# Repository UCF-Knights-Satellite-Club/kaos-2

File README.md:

# kaos-2

KAOS-2 HAB technology demonstration: a high-altitude balloon payload built around a Raspberry Pi Pico flight computer, two Raspberry Pi Zero 2 W camera recorders, and a LightAPRS tracker.

Plan and design notes: [`KAOS_PLAN.md`](KAOS_PLAN.md) and [`KAOS-2_Documentation.md`](KAOS-2_Documentation.md).

## Layout

| Folder | Contents |
|---|---|
| [`Software/`](Software/) | Flight computer code (Pico, Arduino core) |
| [`Electrical/KAOS-2_MainPCB/`](Electrical/KAOS-2_MainPCB/) | Main PCB KiCad project (`KAOS-2_Main.kicad_pro`), with its symbol and footprint library |
| [`Electrical/Symbols/`](Electrical/Symbols/), [`Electrical/Footprints/`](Electrical/Footprints/) | Shared KiCad symbol library and extra footprints (SCD30) |
| [`Test_Modules/`](Test_Modules/) | Bench tests for each module: LightAPRS 2.0 / HAB firmware, BMP388 (C SDK and Arduino), SCD30 (incl. calibration utility), SD card, clock, buzzer, MOSFET, Pico 2 W, and the Pi Zero camera recorder (`Camera/Video_Recorder/`) |
| Root images | Pinouts for the Pico, Pi Zero 2 W and LightAPRS |

## Open items

- **Two flight software versions.** [`Software/KAOS-2.ino`](Software/KAOS-2.ino) (559 lines, last changed 2026-09-21) and [`Software/KAOS-2/KAOS-2.ino`](Software/KAOS-2/KAOS-2.ino) (809 lines, last changed 2026-07-17) differ. Pick the flight version and delete or archive the other.
- **Not yet on GitHub:** the APRS PCB layout and the radio filter test board.
- The main PCB's symbol library (`Electrical/KAOS-2_MainPCB/KAOS-2.kicad_sym`) and the shared one (`Electrical/Symbols/KAOS-2.kicad_sym`) have drifted apart; merge them into one.

## History

Imported from [ColdBloodV/KSC](https://github.com/ColdBloodV/KSC) (`KAOS-2/`) with its commit history. Content from unmerged branches there was added too: the SCD30 calibration utility (`Star-Eater-patch-4`), the BMP_C README (`Star-Eater-patch-2`) and a `2Wscript.py` comment fix (`ColdBloodV-patch-1`).

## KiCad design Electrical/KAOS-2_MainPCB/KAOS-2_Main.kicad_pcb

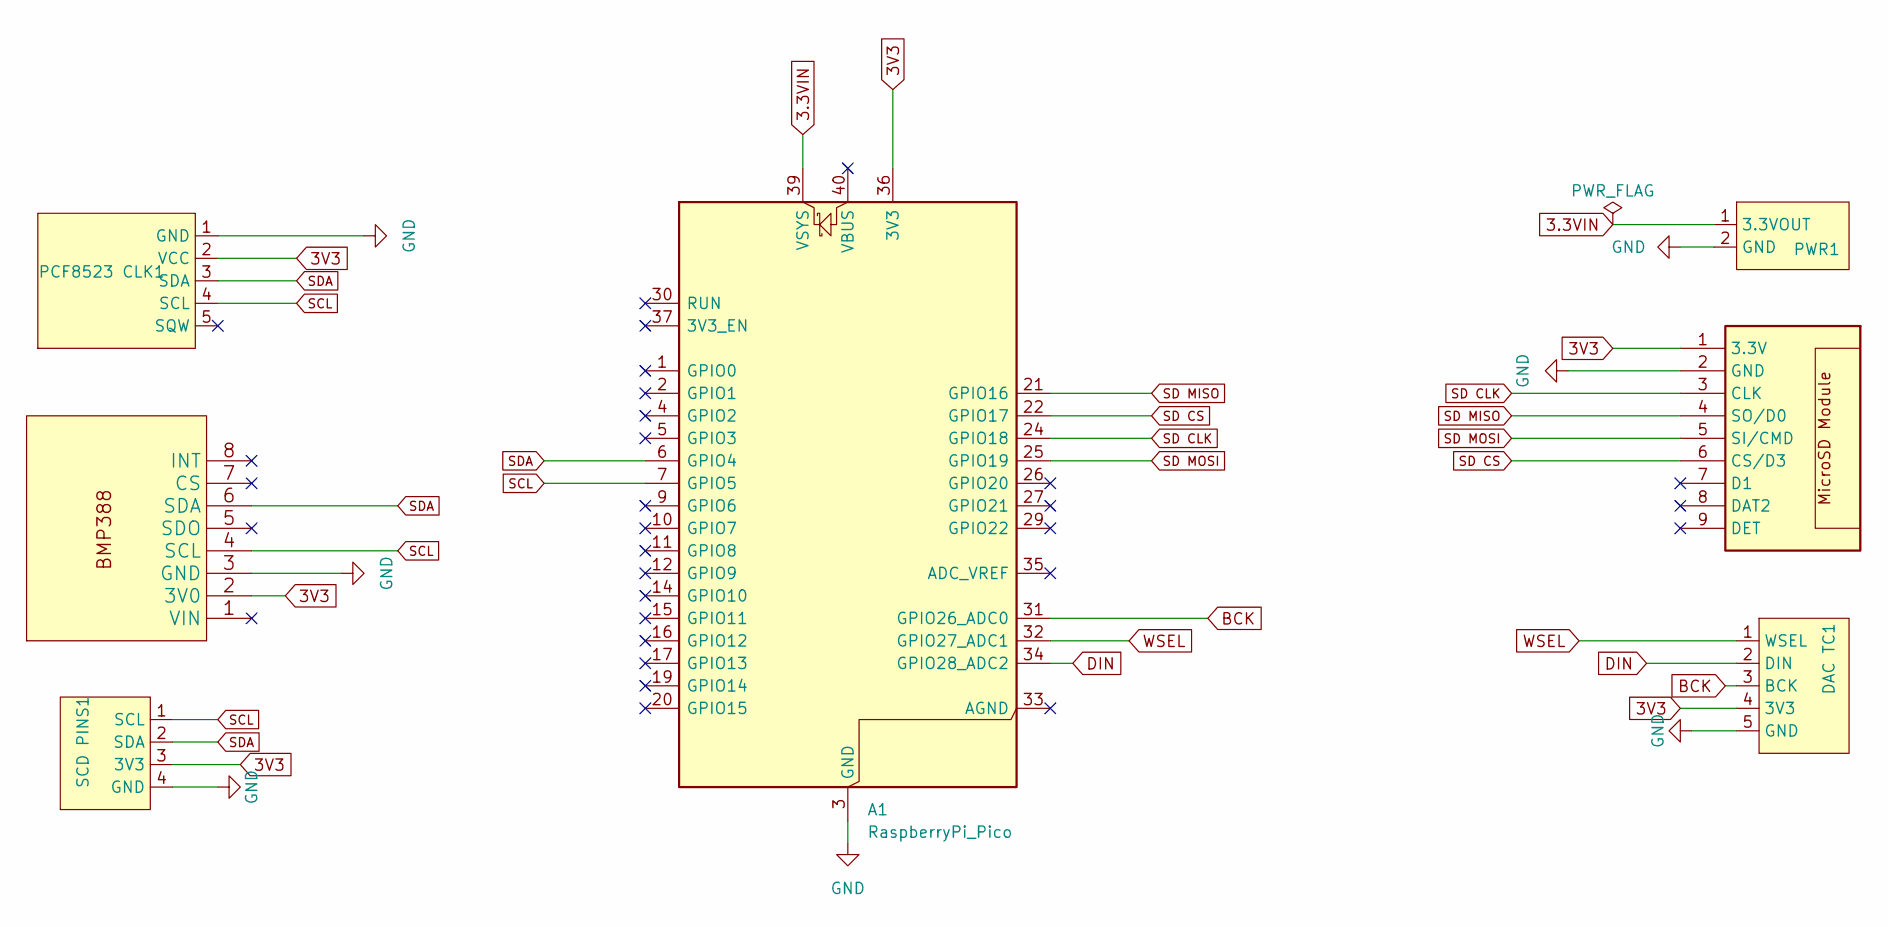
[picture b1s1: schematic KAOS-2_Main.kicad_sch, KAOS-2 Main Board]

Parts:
A1: RaspberryPi_Pico; RaspberryPi_Pico_Common_Unspecified
D1: BMP388
DAC TC1: DAC TC
PCF8523 CLK1: PCF8523 CLK
PWR1: PWR
SCD PINS1: SCD PINS
s1: MIRCOSD MODULE

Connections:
3.3VIN: A1.39 (VSYS), PWR1.1 (3.3VOUT)
3V3: A1.36 (3V3), D1.2 (3V0), DAC TC1.4 (WSEL), PCF8523 CLK1.2 (VCC), SCD PINS1.3 (3V3), s1.1 (3.3V)
BCK: A1.31 (GPIO26_ADC0), DAC TC1.3 (BCK)
DIN: A1.34 (GPIO28_ADC2), DAC TC1.2 (DIN)
GND: A1.3 (GND), A1.8 (GND), A1.13 (GND), A1.18 (GND), A1.23 (GND), A1.28 (GND), A1.38 (GND), D1.3 (GND), DAC TC1.5 (WSEL), PCF8523 CLK1.1 (GND), PWR1.2 (GND), SCD PINS1.4 (SCL), s1.2 (GND)
SCL: A1.7 (GPIO5), D1.4 (SCL), PCF8523 CLK1.4 (SCL), SCD PINS1.1 (SCL)
SD CLK: A1.24 (GPIO18), s1.3 (CLK)
SD CS: A1.22 (GPIO17), s1.6 (CS/D3)
SD MISO: A1.21 (GPIO16), s1.4 (SO/D0)
SD MOSI: A1.25 (GPIO19), s1.5 (SI/CMD)
SDA: A1.6 (GPIO4), D1.6 (SDA), PCF8523 CLK1.3 (SDA), SCD PINS1.2 (SDA)
WSEL: A1.32 (GPIO27_ADC1), DAC TC1.1 (WSEL)

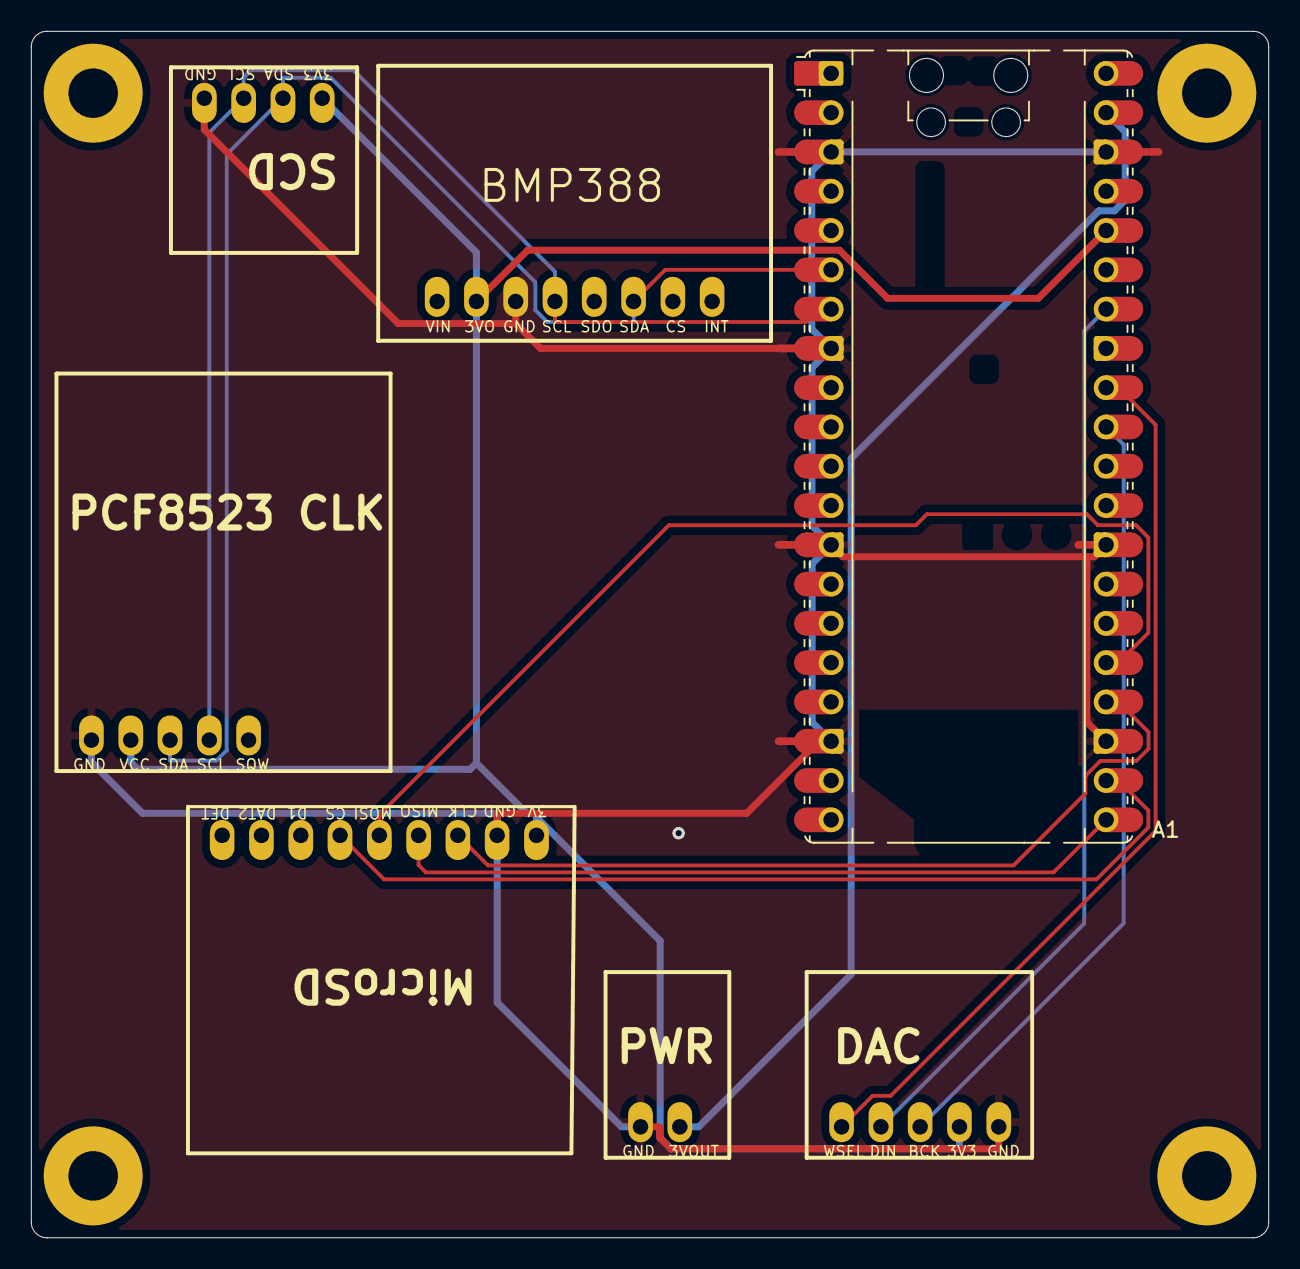
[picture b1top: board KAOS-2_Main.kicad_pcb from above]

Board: 2 copper layers, 80.0 x 78.0 mm, 11 parts (0 on the bottom side), 12 nets.

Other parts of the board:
H1, H2, H3, H4: MountingHole_3.2mm_M3_Pad

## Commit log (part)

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2026-05-25 Fix_Directory
2026-05-28 T-Sat 2A Zip file of Symbols and Footprints
    KiCAD Symbols and Footprints folder that contains items that will probably be reused in KAOS-2
2026-05-31 fixed footprints
2026-05-31 Update KAOS_PLAN with material and component changes
2026-05-31 Revise KAOS-2 plan with updates and clarifications
    Updated the KAOS-2 plan with new considerations, module details, and fixes. Reorganized sections for clarity and added links for resources.
2026-05-31 Remove pricing from module list in KAOS_PLAN.md
2026-05-31 Revise KAOS-2 documentation with updates and corrections
    Updated documentation for KAOS-2, including changes to the Regulator section, antenna redesign notes, and added details on GND and Airtag usage.
2026-05-31 updated Documentation
2026-06-10 Update documentation with regulator and tracking details
    Added notes on regulator overheating and alternative tracking options.
2026-06-12 Move KAOS-2 test modules into project folder
2026-06-16 Add SCD30 Kicad footprint and symbol
2026-06-16 fix directory
2026-06-25 Capture IMX519 photos after video chunks
2026-06-30 Add FAA notification details for launch day
    Added launch day requirements for FAA notification.
